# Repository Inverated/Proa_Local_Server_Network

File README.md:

# Hardware

Electrical simulation used for the build can be found at [Solar Proa](https://github.com/shipshape-marine/solar-proa/tree/main/src/electrical_simulation).

KiCad build file [here](./Hardware%20Schematics/ADC%20Power%20Sensor%20Design/).

# Framework

Network of ESP32 microcontrollers with a Raspberry Pi 4 acting as a local server. ESP32 reading the sensors (slave) communicates bi-directionally via ESP-NOW where the main (Master) ESP32 sends the data to the raspberry pi via Serial communication.

ESP-NOW used for its low latency and low power consumption while being very easy to setup (<10 lines to setup + 2 function that runs when receiving or sending data), while Serial is used for its reliability and ease of use.

Both Serial and ESP-NOW allows for bi-communication, allowing the raspberry pi to send command (zeroing, start, stop, etc.) to specific ESP32s (IMU), while the ESP32s sends data to the raspberry pi at the same time.

[Template for communicating with the master node](./firmware/ESP32/template_sender_firmware//). Note that the mac address need to be changed to the master node's mac address in order for the ESP32 to send data to the master node.

# Code Structure

ExpressJs backend api + Serial reading

React frontend with MUI dashboard template

- https://github.com/mui/material-ui/tree/v9.0.1/docs/data/material/getting-started/templates/dashboard
- A shit template that mixes ts, js and tsx, jsx and poor code organisation

# Proa Local Server Network — Step by step Setup Guide

## Part 1: Running the App

1. `cd` into `PROA_LOCAL_SERVER_NETWORK`.
2. Ensure npm is installed on your system.
3. Run `npm run install:yarn`.
4. Run `yarn start:all`.
   - This automatically builds the React app and runs it with Node.js.
5. Open `http://localhost:4000` in your browser.
6. Dev panel access: username=admin   password=admin

---

## Part 2: Raspberry Pi 4 Setup (Everything else after this is for setting up on raspberry pi)

Using Raspberry Pi Lite OS for fast boot time in case of downtime.
> A UPS is included, but fast boot time and proper recovery steps are still essential.

### 2.1 Initial Setup (from a fresh install via Raspberry Pi Imager)

If ssh does not work, you may need to connect the Pi to an external screen and keyboard to enable it.
1. Connect the Pi to an external screen (micro HDMI) and keyboard.
2. Log in with the username and password created during Imager setup.
3. Enable and start SSH:
   ```bash
   sudo systemctl enable ssh
   sudo systemctl start ssh
   ```

### 2.2 SSH into the Pi from Another Computer

1. On Raspberry Pi 4 and below (check your model first), the USB-C port is power-only — you'll need an additional Ethernet cable to connect.

### 2.3 Optimize Boot Time

1. Open the quick system settings GUI to connect to a WiFi network for update purposes:
   ```bash
   sudo raspi-config
   ```
2. Disable unneeded services for a faster boot:
   ```bash
   sudo systemctl disable NetworkManager-wait-online.service
   sudo systemctl mask NetworkManager-wait-online.service
   sudo systemctl disable cloud-init-local.service
   sudo systemctl disable cloud-init-main.service
   sudo systemctl disable cloud-config.service
   sudo systemctl disable cloud-final.service
   sudo systemctl disable apt-daily-upgrade.service
   sudo systemctl disable apt-daily.service
   ```
3. Note: boot time will still be around 20 seconds.

### 2.4 Verify Network Connectivity (Before Upgrading Packages)
 
`apt full-upgrade` requires a working internet connection — check this first if you hit connection errors.
 
1. Check if Wi-Fi is scanning networks:
```bash
   sudo iwlist wlan0 scan | grep ESSID
```
2. If nothing comes back (Wi-Fi is down), bring it back up:
```bash
   sudo rfkill unblock wifi
   sudo ip link set wlan0 up
   sudo nmcli radio wifi on
   sudo systemctl restart wpa_supplicant
   sudo systemctl restart NetworkManager
```
3. Re-run the scan command from step 1 to confirm networks now appear, then proceed.

### 2.5 Download Required Packages

1. Update and install system packages:
   ```bash
   sudo apt full-upgrade
   sudo apt install git nodejs npm curl hostapd dnsmasq dhcpcd5 iptables nginx -y
   sudo npm install yarn -g
   ```
2. Install nvm and Node LTS:
   ```bash
   curl -o- https://raw.githubusercontent.com/nvm-sh/nvm/v0.40.1/install.sh | bash
   source ~/.bashrc
   nvm install --lts
   nvm use node
   ```

### 2.6 Set Up the Git Repo

1. Create a directory and clone the repo:
   ```bash
   mkdir apps
   cd apps
   git clone https://github.com/Inverated/Proa_Local_Server_Network advisor
   cd advisor/
   yarn install
   yarn start:all
   ```
2. Force-stop the process once the initial build completes.

3. Copy '.env' into proa_advisor

### 2.7 Set Up the Network (Wi-Fi Access Point)

1. Stop the AP-related services before configuring them:
   ```bash
   sudo systemctl stop hostapd
   sudo systemctl stop dnsmasq
   ```
2. Mark `wlan0` as unmanaged by NetworkManager. Edit:
   ```bash
   sudo nano /etc/NetworkManager/conf.d/unmanaged.conf
   ```
   Add:
   ```ini
   [keyfile]
   unmanaged-devices=interface-name:wlan0
   ```
3. Set a static IP for `wlan0`. Edit:
   ```bash
   sudo nano /etc/dhcpcd.conf
   ```
   Add:
   ```ini
   interface wlan0
   static ip_address=192.168.4.1/24
   nohook wpa_supplicant
   ```
4. Restart the dhcpcd service:
   ```bash
   sudo systemctl restart dhcpcd
   ```
5. Configure hostapd. Edit:
   ```bash
   sudo nano /etc/hostapd/hostapd.conf
   ```
   Add:
   ```ini
   interface=wlan0
   driver=nl80211

   ssid=Proa_II

   hw_mode=g
   channel=6

   country_code=SG

   wmm_enabled=1

   auth_algs=1
   ignore_broadcast_ssid=0

   wpa=2
   wpa_passphrase=password

   wpa_key_mgmt=WPA-PSK
   rsn_pairwise=CCMP
   ```
6. Point the hostapd daemon at that config. Edit:
   ```bash
   sudo nano /etc/default/hostapd
   ```
   Add:
   ```ini
   DAEMON_CONF="/etc/hostapd/hostapd.conf"
   ```
7. Back up and replace the dnsmasq config:
   ```bash
   sudo mv /etc/dnsmasq.conf /etc/dnsmasq.conf.orig
   sudo nano /etc/dnsmasq.conf
   ```
   Add:
   ```ini
   interface=wlan0

   dhcp-range=192.168.4.2,192.168.4.100,255.255.255.0,24h

   dhcp-option=3,192.168.4.1
   dhcp-option=6,192.168.4.1

   address=/#/192.168.4.1
   ```
8. Unmask and enable the AP services, then restart networking and start them:
   ```bash
   sudo systemctl unmask hostapd
   sudo systemctl enable hostapd
   sudo systemctl enable dnsmasq

   sudo systemctl restart wpa_supplicant
   sudo systemctl restart NetworkManager
   sudo systemctl start hostapd
   sudo systemctl start dnsmasq
   ```
9. Verify `wlan0` is running in AP mode:
    ```bash
    iw dev wlan0 info
    ```
    If the type isn't `AP`, run `sudo reboot` and check again.

10. Give access to user to run nmcli over Node
    ```bash
    sudo nano /etc/polkit-1/rules.d/50-nmcli.rules
    ```
    Add:
    ```javascript
    polkit.addRule(function(action, subject) {
        if (action.id.indexOf("org.freedesktop.NetworkManager.") === 0 &&
            subject.user == "admin") {
            return polkit.Result.YES;
        }
    });
    ```
11. Restart polkit:
    ```bash
    sudo systemctl restart polkit
    ```

### 2.9 Auto-Redirect Port 80 to the App (Port 4000)

1. Create the redirect service:
   ```bash
   sudo nano /etc/nginx/sites-available/solarproa
   ```
   Add:
   ```ini
   server {
    listen 80;
    server_name solarproa.local;

    location / {
        proxy_pass http://127.0.0.1:4000;

        proxy_set_header Host $host;
        proxy_set_header X-Real-IP $remote_addr;
        proxy_set_header X-Forwarded-For $proxy_add_x_forwarded_for;
        proxy_set_header X-Forwarded-Proto $scheme;
    }
   }
   ```
2. Enable and start it:
   ```bash
   sudo ln -s /etc/nginx/sites-available/solarproa /etc/nginx/sites-enabled/
   ```

3. Test it:
   ```bash
   sudo nginx -t
   ```

4. Restart nginx service
   ```bash
   sudo systemctl restart nginx
   ```

   When connected to the same network as the raspberry pi, go to http://solarproa.local

### 2.8 Set Up Auto-Start on Boot

1. Create the app service:
   ```bash
   sudo nano /etc/systemd/system/solarproa-advisor.service
   ```
   Add:
   ```ini
    [Unit]
    Description=Solar Proa Advisor
    After=network-online.target
    Wants=network-online.target

    [Service]
    Type=simple
    User=admin
    WorkingDirectory=/home/admin/apps/advisor/proa_advisor

    Environment=NODE_ENV=production
    Environment=NVM_DIR=/home/admin/.nvm

    ExecStart=/bin/bash -c 'source "$NVM_DIR/nvm.sh" && nvm use default && exec yarn start'

    Restart=always
    RestartSec=5

    [Install]
    WantedBy=multi-user.target
   ```
2. Enable and start it:
   ```bash
   sudo systemctl daemon-reload
   sudo systemctl enable solarproa-advisor
   sudo systemctl start solarproa-advisor
   ```
3. Check the logs:
   ```bash
   journalctl -u solarproa-advisor -f
   ```

### 2.10 Note: AP vs. Wi-Fi Receiver Mode

The Wi-Fi chip can only act as **either** an access point **or** a receiver at one time — switch back to receiving, or use an external Wi-Fi adapter.

1. Check the new Wi-Fi receiver's interface name (should be `wlan1`).
2. Connect to a network on that interface:
   ```bash
   sudo nmcli device wifi connect "YourSSID" password "YourPassword" ifname wlan1
   ```

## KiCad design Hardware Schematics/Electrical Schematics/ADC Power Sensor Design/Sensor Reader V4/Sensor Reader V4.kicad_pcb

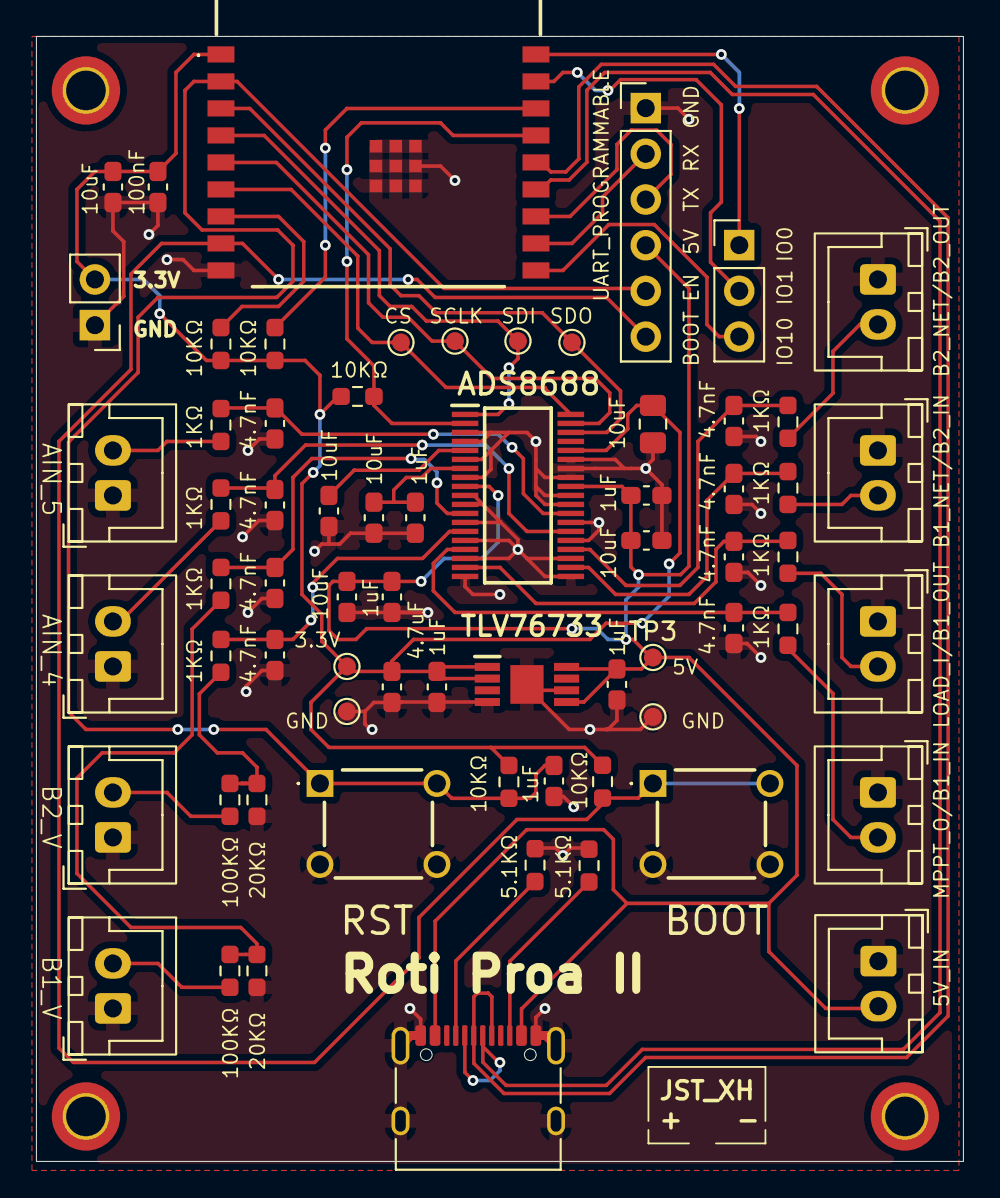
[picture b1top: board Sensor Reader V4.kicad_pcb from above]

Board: 2 copper layers, 51.5 x 62.5 mm, 67 parts (0 on the bottom side), 41 nets.

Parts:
C2, C4, C7, C9, C10, C13: 1uF; C_0603_1608Metric_Pad1.08x0.95mm_HandSolder
C3: 4.7uF; C_0603_1608Metric_Pad1.08x0.95mm_HandSolder
C5, C8, C12, C20, C23: 10uF; C_0603_1608Metric_Pad1.08x0.95mm_HandSolder
C6: 100nF; C_0603_1608Metric_Pad1.08x0.95mm_HandSolder
C11: 10uF; C_0805_2012Metric_Pad1.18x1.45mm_HandSolder
C14, C15, C16, C17, C18, C19, C21, C22: 4.7nF; C_0603_1608Metric_Pad1.08x0.95mm_HandSolder
IC1: TLV76733DGNR; SOP65P490X110-9N
IC2: ESP32-C3-WROOM-02-H4; ESP32C3WROOM02H4
J1: USB_C_Receptacle_USB2.0_16P; USB_C_Receptacle_XKB_U262-16XN-4BVC11
J2: GPIO; PinHeader_1x03_P2.54mm_Vertical
J6: Exposed_UART; PinHeader_1x06_P2.54mm_Vertical
J7: Batt1_V; JST_XH_B2B-XH-A_1x02_P2.50mm_Vertical
J8: Batt2_V; JST_XH_B2B-XH-A_1x02_P2.50mm_Vertical
J9: M_OUT/B1_In; JST_XH_B2B-XH-A_1x02_P2.50mm_Vertical
J10: L_I/B1_Out; JST_XH_B2B-XH-A_1x02_P2.50mm_Vertical
J11: B1_Net/B2_In; JST_XH_B2B-XH-A_1x02_P2.50mm_Vertical
J12: B2_Net/B2_Out; JST_XH_B2B-XH-A_1x02_P2.50mm_Vertical
J13: AIN_4; JST_XH_B2B-XH-A_1x02_P2.50mm_Vertical
J14: AIN_5; JST_XH_B2B-XH-A_1x02_P2.50mm_Vertical
J15: 5V_Input; JST_XH_B2B-XH-A_1x02_P2.50mm_Vertical
J16: 3.3V_Output; PinHeader_1x02_P2.54mm_Vertical
R2, R20: 5.1KΩ; R_0603_1608Metric_Pad0.98x0.95mm_HandSolder
R3, R4, R5, R6, R7: 10kΩ; R_0603_1608Metric_Pad0.98x0.95mm_HandSolder
R8, R9, R10, R11, R12, R13, R14, R15: 1kΩ; R_0603_1608Metric_Pad0.98x0.95mm_HandSolder
R16, R18: 100kΩ; R_0603_1608Metric_Pad0.98x0.95mm_HandSolder
R17, R19: 20kΩ; R_0603_1608Metric_Pad0.98x0.95mm_HandSolder
SW1: BOOT_Btn; TS0266100BK100LCRD
SW2: EN_Btn; TS0266100BK100LCRD
TP1, TP2, TP3, TP4, TP5, TP6, TP7, TP8: TestPoint; TestPoint_Pad_D1.0mm
U3: ADS8688; SOP50P640X120-38N

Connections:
+3.3V: C3.1, C6.1, C11.1, C13.1, C23.1, IC1.1 (OUT), IC1.2 (SNS), IC2.1 (3V3), J16.2, R3.1, R4.1, R5.1, R6.1, R7.2, TP1.1 (1_1), U3.34 (DVDD)
+5V: C2.1, C9.1, C10.1, C12.1, C20.1, IC1.5 (EN), IC1.8 (IN), J1.A4 (VBUS), J1.A9 (VBUS), J1.B4 (VBUS), J1.B9 (VBUS), J6.4, J15.2, TP3.1 (1_1), U3.9 (AVDD), U3.30 (AVDD)
AIN_4: J13.2, R12.1
AIN_5: J14.2, R13.1
BOOT: IC2.8 (IO9), J6.6, R4.2, SW1.1, SW1.2
Batt1_Net/Batt2_In: J11.2, R10.1
Batt1_V: J7.2, R16.1
Batt2_Net/Batt2_Out: J12.2, R11.1
Batt2_V: J8.2, R18.1
CS: IC2.6 (IO7), TP4.1 (1_1), U3.38 (~CS)
EN: C4.1, IC2.2 (EN), J6.5, R3.2, SW2.1, SW2.2
GND: C2.2, C3.2, C4.2, C5.2, C6.2, C7.2, C8.2, C9.2, C10.2, C11.2, C12.2, C13.2, C14.1, C15.1, C16.1, C17.1, C18.1, C19.1, C20.2, C21.1, C22.1, C23.2, IC1.4 (GND_1), IC1.6 (GND_2), IC1.9 (EP), IC2.9 (GND_1), IC2.19 (GND_2), IC2.20 (GND_3), IC2.21 (GND_4), IC2.22 (GND_5), IC2.23 (GND_6), IC2.24 (GND_7), IC2.25 (GND_8), IC2.26 (GND_9), IC2.27 (GND_10), J1.A1 (GND), J1.A12 (GND), J1.B1 (GND), J1.B12 (GND), J1.SH (SHIELD), J6.1, J7.1, J8.1, J9.1, J10.1, J11.1, J12.1, J13.1, J14.1, J15.1, J16.1, R2.1, R17.2, R19.2, R20.2, SW1.3 (K), SW1.4 (A), SW2.3 (K), SW2.4 (A), TP2.1 (1_1), TP8.1 (1_1), U3.3 (DAISY), U3.4 (~REFSEL), U3.6 (REFGND), U3.8 (AGND), U3.10 (AUX_IN), U3.11 (AUX_GND), U3.13 (AIN_6GND), U3.15 (AIN_7GND), U3.17 (AIN_0GND), U3.19 (AIN_1GND), U3.20 (AIN_2GND), U3.22 (AIN_3GND), U3.24 (AIN_4GND), U3.26 (AIN_5GND), U3.28 (AGND), U3.29 (AGND), U3.31 (AGND), U3.32 (AGND), U3.33 (DGND)
GPIO0: IC2.18 (IO0), J2.1
GPIO1: IC2.17 (IO1), J2.2
GPIO10: IC2.10 (IO10), J2.3
Load_In/Batt1_Out: J10.2, R9.1
MPPT_Out/Batt1_In: J9.2, R8.1
unnamed: IC2.16 (IO2), R5.2
unnamed: IC2.7 (IO8), R6.2
unnamed: J1.A5 (CC1), R2.2
unnamed: J1.B5 (CC2), R20.1
unnamed: R14.1, R16.2, R17.1
unnamed: R15.1, R18.2, R19.1
unnamed: C21.2, R8.2, U3.16 (AIN_0P)
unnamed: C22.2, R9.2, U3.18 (AIN_1P)
unnamed: C17.2, R10.2, U3.21 (AIN_2P)
unnamed: C18.2, R11.2, U3.23 (AIN_3P)
unnamed: C19.2, R12.2, U3.25 (AIN_4P)
unnamed: C14.2, R13.2, U3.27 (AIN_5P)
unnamed: C15.2, R14.2, U3.12 (AIN_6P)
unnamed: C16.2, R15.2, U3.14 (AIN_7P)
unnamed: C7.1, C8.1, U3.7 (REFCAP)
unnamed: C5.1, U3.5 (REFIO)
RST: IC2.15 (IO3), R7.1, U3.2 (~RST/PD)
RX: IC2.11 (RXD), J6.2
SCLK: IC2.5 (IO6), TP5.1 (1_1), U3.37 (SCLK)
SDI: IC2.4 (IO5), TP6.1 (1_1), U3.1 (SDI)
SDO: IC2.3 (IO4), TP7.1 (1_1), U3.36 (SDO)
TX: IC2.12 (TXD), J6.3
USB_D+: IC2.14 (IO19), J1.A6 (D+), J1.B6 (D+)
USB_D-: IC2.13 (IO18), J1.A7 (D-), J1.B7 (D-)

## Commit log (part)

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2026-03-22 Initialise website for cloning
2026-03-23 serial port scanner
2026-03-25 setup esp receiver code
2026-05-08 init
2026-05-14 setup for react frontend instead of pure express
2026-05-16 Integrate MUI template
2026-05-16 Sidebar
2026-05-17 sqlite setup
2026-05-17 update model
2026-05-18 kalman gain partial implementation
2026-05-30 complete basic ekf implementation
2026-06-03 fix model
2026-06-04 test data implemetation
2026-06-04 untested serial parser
2026-06-06 serial reading
2026-06-09 filter test update
2026-06-14 LiFePO4 data
2026-06-17 working filter
2026-06-18 event source connection success
2026-06-19 tune filter 1
2026-06-19 fixed stylign
2026-06-20 model tune 2
2026-06-20 ekf recovery
2026-06-21 fix nav bar and clean log statements
2026-06-21 uodate db model
2026-06-21 completed recovery chart
2026-06-22 combine multiple db transactions
2026-06-23 tuned alt batt
2026-06-23 time estimate completed
2026-06-23 fix wrong battery rc mapping
2026-06-25 adjust chart ui
2026-06-26 concurrently yarn script
2026-06-26 modularise power byte parser
2026-06-27 automatic react build
2026-06-27 reorder template
2026-06-27 logging statement update on init
2026-06-28 fixed bbreadcrumbs
2026-06-30 fix serial parser not skipping on checksum fail
2026-06-30 main batt test data
